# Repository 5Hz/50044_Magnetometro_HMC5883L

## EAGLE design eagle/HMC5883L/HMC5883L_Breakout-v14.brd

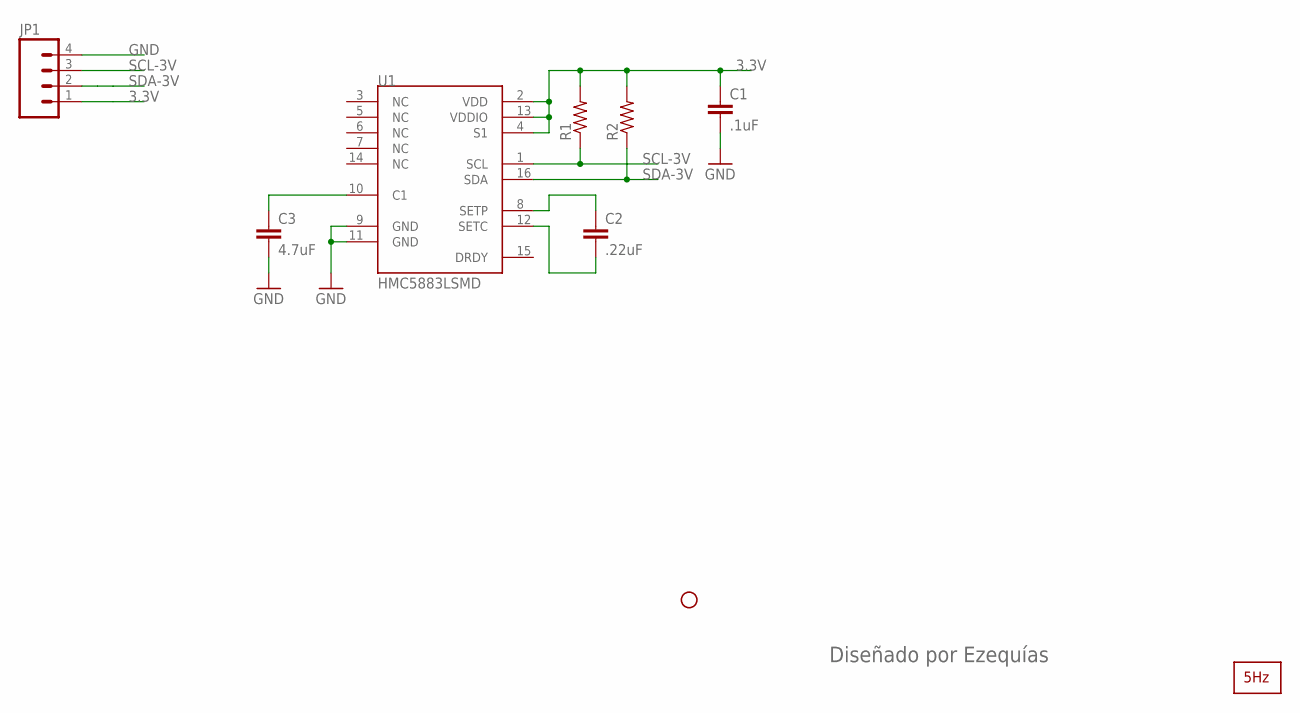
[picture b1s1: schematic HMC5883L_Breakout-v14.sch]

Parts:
C1: .1uF; 0603-CAP
C2: .22uF; 0603-CAP
C3: 4.7uF; 0603-CAP
JP1: M04PTH; 1X04
JP4: STAND-OFF
R1, R2: RESISTORPTH-1/6W; 1/6W-RES
U1: HMC5883LSMD; 16LPCC
U$1: LOGO2_SILK5MM; LOGO2_5MM

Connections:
3.3V: C1.1, JP1.1, R1.2, R2.2, U1.2 (VDD), U1.4 (S1), U1.13 (VDDIO)
GND: C1.2, C3.2, JP1.4, U1.9 (GND), U1.11 (GND)
unnamed: C3.1, U1.10 (C1)
unnamed: C2.1, U1.8 (SETP)
unnamed: C2.2, U1.12 (SETC)
SCL-3V: JP1.3, R1.1, U1.1 (SCL)
SDA-3V: JP1.2, R2.1, U1.16 (SDA)

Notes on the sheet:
Diseñado por Ezequías

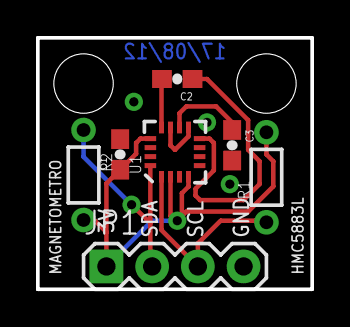
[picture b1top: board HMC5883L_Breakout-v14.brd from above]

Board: 2 copper layers, 15.2 x 14.0 mm, 10 parts (1 on the bottom side), 7 nets.

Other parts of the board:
JP2: STAND-OFF

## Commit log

2014-01-13 creación
